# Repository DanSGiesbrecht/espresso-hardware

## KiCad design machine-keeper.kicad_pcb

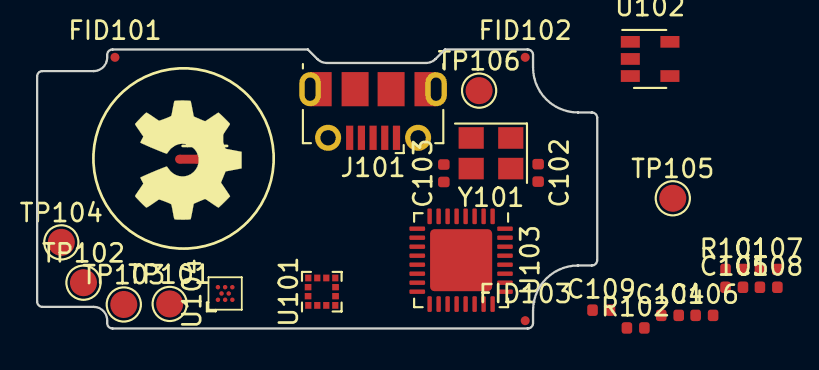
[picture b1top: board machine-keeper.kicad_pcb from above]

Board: 4 copper layers, 31.1 x 15.5 mm, 27 parts (0 on the bottom side), 12 nets, no tracks yet.

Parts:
C102, C103: C_Small; C_0402_1005Metric
C104, C105, C106, C107, C108, C109: 0.1uF; C_0402_1005Metric
FID101, FID102, FID103: TestPoint; Fiducial_0.5mm_Dia_1mm_Outer
J101: USB_B_Micro; USB_Micro-B_Molex-105017-0001
LOGO101: Logo_Open_Hardware_Small; OSHW-Symbol_6.7x6mm_SilkScreen
NT101: Net-Tie_2; NetTie-2_SMD_Pad0.5mm
R101: 0R-DNU; R_0402_1005Metric
R102: 0R; R_0402_1005Metric
TP101, TP102, TP103, TP104, TP105, TP106: TestPoint; TestPoint_Pad_D1.5mm
U101: LIS2HH12; LGA-12_2x2mm_P0.5mm
U102: TLV71333PDBV; SOT-23-5
U103: STM32F302K8Ux; QFN-32-1EP_5x5mm_P0.5mm_EP3.45x3.45mm
U104: AT25DF041x-UxN-x; WLCSP-8_1.58x1.63x0.35mm_Layout3x5_P0.35x0.4mm_Ball0.25mm_P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
Y101: Crystal_GND24; Crystal_SMD_3225-4Pin_3.2x2.5mm

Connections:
/CAP_TOUCH: NT101.1, NT101.2
/MCU_RST: TP101.1, U103.4
/SWCLK: TP103.1, U103.24
/SWDIO: TP102.1, U103.23
/USB_DM: J101.2, U103.21
/USB_DP: J101.3, U103.22
GND: C102.2, C103.2, C104.2, C105.2, C106.2, J101.5, J101.6, R102.2, TP106.1, U101.6, U101.7, U101.8, U102.2, U103.6, U103.16, U103.32, U103.33, U104.B2, Y101.2, Y101.4
unnamed: C102.1, U103.2, Y101.1
unnamed: C103.1, U103.3, Y101.3
unnamed: R101.2, R102.1, U103.31
VBUS: J101.1, U102.1, U102.3
VCC: C104.1, C105.1, C106.1, R101.1, TP105.1, U103.1, U103.5, U103.17

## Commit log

2018-09-21 Add .gitattributes, .gitignore
2018-10-14 Add initial project files
2018-10-21 Work on schematic
2018-10-21 Add board outline DXF.
2018-10-22 Initial PCB placement, work on schematic.
